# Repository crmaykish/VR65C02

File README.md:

# VR65C02
A 6502 computer system with an ATmega4809 simulating all of the memory and I/O. Two ICs are enough to run native 6502 code on the real silicon. All of the 6502's interactions with the outside world go through the microcontroller.

It's like the 6502 is wearing the ATmega as a VR headset! (AVR headset?)

## Background

### TL;DR

- Real 6502 code running on a real 6502
- ATmega4809 microcontroller emulates everything else
- 6502 is programmed by uploading an Arduino sketch
- 5KB of emulated RAM, up to 32KB emulated ROM
- Memory-mapped UART, GPIO, and I2C peripherals for the 6502
- Eye-watering clock speed of ~250 kHz!

### Why?

Why not? This project started as a weekend experiment to see if I could run a 6502 CPU without having to use a real ROM chip. That quickly turned into "Can I run 6502 code on a real CPU without any real memory or peripherals attached. The answer is yes.

This computer is not fast. It's not practical, but it is kind of fun.

### Why not a Raspberry Pi Pico or FPGA?

Those would both likely be better choices, but to be totally honest, the availability of the ATmega4809 in a 40 pin DIP package is what sold me. I like the aesthetic of two DIP ICs. That's really it.

## Features

### Memory Emulation

VR65C02 is a fully functional computer system. The ATmega microcontroller provides emulated RAM and ROM as well as a passthrough UART and four GPIO pins that the 6502 can access.

The microcontroller controls the RESET and CLOCK lines of the CPU, so all memory access is handled synchronously by the Arduino code. For each bus cycle, the microcontroller reads the address bus and R/W pin from the CPU. If the CPU is reading a memory address, the microcontroller will decode the address into a memory value or an I/O operation and write the appropriate value out to the data bus. On a write cycle, the microcontroller reads the data bus value into its simulated RAM or updates the appropriate I/O system. The microcontroller implements address decoding in code in a similar way to a traditional system using logic gates or PLDs.

Both RAM and ROM are backed by large byte arrays in the microcontroller's memory, the RAM using onboard SRAM and the ROM using onboard Flash.

### I/O Emulation

The UART is a memory-mapped I/O device from the perspective of the 6502, similar to a 6551 ACIA. The CPU can read and write bytes and the microcontroller passes them through to one of its native serial ports.

Similarly, there are four GPIO pins accessible as a memory-mapped register to the 6502.

These GPIO ports have two alternate functions. If SOFT_RESET is defined in [memory_map.h](src/6502_vr_goggles/memory_map.h), then GPIO pin 0 will function as a reset pin for the 6502. It does not reset the Arduino, but it triggers the Arduino to reset the 6502. If soft reset is enabled, pin 0 cannot be used as a normal GPIO pin.

I2C devices can also be attached to the GPIO pins. GPIO 2 and 3 double as SDA and SCL respectively. The Arduino provides low level access to the I2C bus through a few memory-mapped registers. The 6502 can enable/disable the I2C bus, set the active peripheral address, and read/write data through these registers.

See [memory_map.h](src/6502_vr_goggles/memory_map.h) for more details.

It should also be possible to implement SPI passthrough in a similar fashion, but I2C is really a better fit for this system, especially considering its slow clock speed and lack of I/O lines. With I2C, a ton of peripherals can be daisy-chained and there is still room for 1 or 2 GPIO pins. I've tested reading a real-time clock module over I2C from the 6502 code (see the `time` command in [monitor.c](src/monitor.c)).

### Memory Map

The memory map of the 6502 is as follows:
1. 5KB "RAM" at 0x0000
2. I/O regisers at 0x7F00
3. 8KB "ROM" at 0xE000

The ATmega4809 has enough flash memory to support up to 32KB of ROM if necessary, but the total onboard SRAM is only 6KB and some is set aside for the Arduino code.

## Software

The core of VR65C02 is the Arduino sketch running on the ATmega4809. As described above, this program simulates the entire bus cycle of the physical 6502 CPU and all of the memory and I/O interactions.

Real 6502 machine code is running on the CPU. This can be assembly or C code compiled with cc65. Since there is no physical ROM or RAM, the code has to live somewhere. My approach is to use the large amount of onboard Flash memory of the ATmega to store this. The main trick of VR65C02 is taking this compiled binary and getting it into the microcontroller Flash as part of the Arduino sketch upload.

### Setup

To build and deploy code to the VR65C02, you'll need to setup the following:
1. Install Arduino to `/opt/local`
2. Install MegaCoreX Arduino package
3. Install cc65 or some other 6502 compiler/assembler
4. Install make (`build-essential` on Debian/Ubuntu)
5. Install Python 3.x

Note: you may need to update the build.sh script if you're on a different platform. Windows will probably require a different approach.

### Building

The build process is done in a single script, [build.sh](src/build.sh). The process looks like this:
1. Compile 6502 C code into a binary ROM file.
2. Run a Python script to convert this binary file into a C header file with a large const array of bytes.
3. Compile the Arduino sketch with this generated header file.
4. Upload Arduino sketch to microcontroller with new 6502 code.

### Programming the ATmega (and by extension the 6502)

Programming the ATmega4809 is done via UPDI. UPDI is a one-wire programming interface that can be implemented over a simple serial port. On VR65C02, the wiring is already done on the board, so a standard FTDI-style USB-UART can be plugged into the onboard UPDI header. In the Arduino IDE, the SerialUPDI programmer included in MegaCoreX at 230400 baud will work just fine. Make sure to set the serial port to the UPDI USB device and not the one plugged into the UART port.

Note: the board and programmer selection is already done in the [build.sh](src/build.sh) script using the `arduino-cli` command.

It's possible to use a single FTDI device and switch between the headers on board for programming versus serial monitoring, but having two different serial ports is a lot more convenient.

## Limitations

All of the limitations of this system come down to hitting the limits of the ATmega4809 itself in one way or another.

### Clock Speed

The main drawback is obviously clock speed. Simulating the whole bus cycle and all of the potential memory and I/O operations of the 6502 on a 20 MHz 8-bit microcontroller is not exactly quick. Measuring the PHI2 output on the CPU with an oscilloscope shows that the effective clock speed is about 257 kHz. Even at this speed, VR65C02 is surprisingly usable for simple GPIO tasks or interacting over the serial port, but it's about 4x slower than a Commodore 64 or Apple II.

Because not all the emulated peripherals respond at the same speed, the effective clock speed is actually somewhat variable depending on the I/O demands of the 6502 code. This doesn't fluctuate too dramatically, but heavy I/O, e.g. polling the serial port, will run at around 257 kHz, whereas no I/O at all will get the clock up to about 270 kHz.

### Not Enough Pins

Besides the slow speed, the other main limitations is the lack of available pins on the ATmega. All 31 available IO pins are being used to connect to the 6502 bus and control signals. Two of the pins are used for the serial port and four are set up as GPIO. The GPIO pins could be used for other things, but there's not a huge number to spare.

In theory, these GPIO pins could be repurposed as chip-select signals to attach some real I/O devices to the system. It wouldn't be a stretch to attach a real RAM chip and have the microcontroller copy the program code from Flash into that RAM. In that scenario, a real clock oscillator could be used and the Arduino would become a slow peripheral using the RDY pin to handle the higher clock rate.

The ATmega4809 is also available in a 48 pin QFP package with quite a few more I/O pins. This might be fun to explore, but it would definitely detract from the DIP aesthetic and make VR65C02 harder to build.

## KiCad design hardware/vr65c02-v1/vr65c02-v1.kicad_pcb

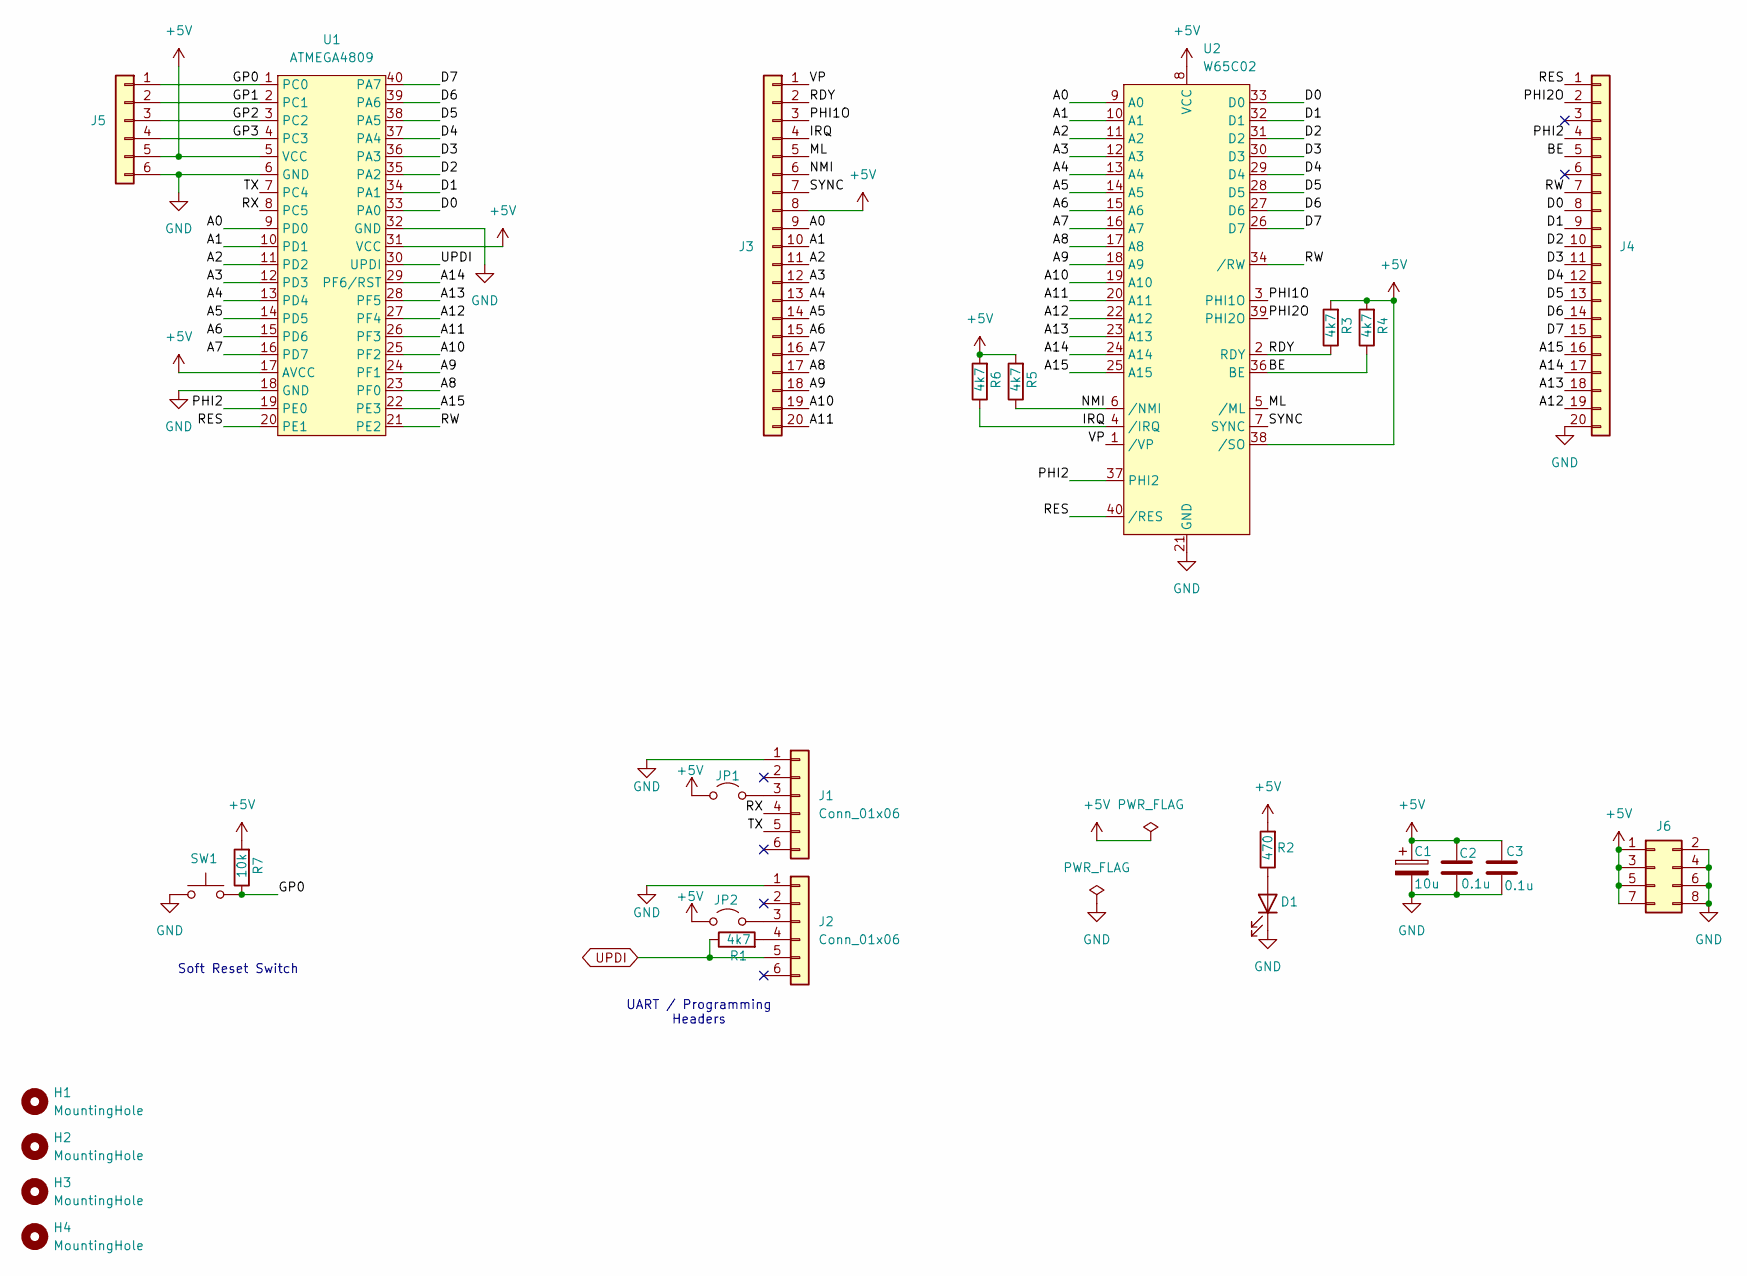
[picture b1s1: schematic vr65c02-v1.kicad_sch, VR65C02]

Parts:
C1: 10u; CP_Radial_D5.0mm_P2.50mm
C2, C3: 0.1u; C_Disc_D4.7mm_W2.5mm_P5.00mm
D1: LED; LED_D5.0mm
H1, H2, H3, H4: MountingHole; MountingHole_3.2mm_M3
J1, J2: Conn_01x06; PinSocket_1x06_P2.54mm_Vertical
J3, J4: Conn_01x20; PinHeader_1x20_P2.54mm_Vertical
J5: Conn_01x06; PinHeader_1x06_P2.54mm_Vertical
J6: Conn_02x04_Odd_Even; PinHeader_2x04_P2.54mm_Vertical
JP1, JP2: Jumper_2_Open; PinHeader_1x02_P2.54mm_Vertical
R1, R3, R4, R5, R6: 4k7; R_Axial_DIN0207_L6.3mm_D2.5mm_P7.62mm_Horizontal
R2: 470; R_Axial_DIN0207_L6.3mm_D2.5mm_P7.62mm_Horizontal
R7: 10k; R_Axial_DIN0207_L6.3mm_D2.5mm_P7.62mm_Horizontal
SW1: SW_Push; SW_PUSH_6mm_H5mm
U1: ATMEGA4809; DIP-40_W15.24mm
U2: W65C02; DIP-40_W15.24mm

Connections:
+5V: C1.1, C2.1, C3.1, J3.8, J5.5, J6.1, J6.3, J6.5, J6.7, JP1.1 (A), JP2.1 (A), R2.2, R3.2, R4.2, R5.2, R6.2, R7.2, U1.5 (VCC), U1.17 (AVCC), U1.31 (VCC), U2.8 (VCC), U2.38 (/SO)
/A0: J3.9, U1.9 (PD0), U2.9 (A0)
/A1: J3.10, U1.10 (PD1), U2.10 (A1)
/A2: J3.11, U1.11 (PD2), U2.11 (A2)
/A3: J3.12, U1.12 (PD3), U2.12 (A3)
/A4: J3.13, U1.13 (PD4), U2.13 (A4)
/A5: J3.14, U1.14 (PD5), U2.14 (A5)
/A6: J3.15, U1.15 (PD6), U2.15 (A6)
/A7: J3.16, U1.16 (PD7), U2.16 (A7)
/A8: J3.17, U1.23 (PF0), U2.17 (A8)
/A9: J3.18, U1.24 (PF1), U2.18 (A9)
/A10: J3.19, U1.25 (PF2), U2.19 (A10)
/A11: J3.20, U1.26 (PF3), U2.20 (A11)
/A12: J4.19, U1.27 (PF4), U2.22 (A12)
/A13: J4.18, U1.28 (PF5), U2.23 (A13)
/A14: J4.17, U1.29 (PF6/RST), U2.24 (A14)
/A15: J4.16, U1.22 (PE3), U2.25 (A15)
/BE: J4.5, R4.1, U2.36 (BE)
/D0: J4.8, U1.33 (PA0), U2.33 (D0)
/D1: J4.9, U1.34 (PA1), U2.32 (D1)
/D2: J4.10, U1.35 (PA2), U2.31 (D2)
/D3: J4.11, U1.36 (PA3), U2.30 (D3)
/D4: J4.12, U1.37 (PA4), U2.29 (D4)
/D5: J4.13, U1.38 (PA5), U2.28 (D5)
/D6: J4.14, U1.39 (PA6), U2.27 (D6)
/D7: J4.15, U1.40 (PA7), U2.26 (D7)
/GP0: J5.1, R7.1, SW1.2, U1.1 (PC0)
/GP1: J5.2, U1.2 (PC1)
/GP2: J5.3, U1.3 (PC2)
/GP3: J5.4, U1.4 (PC3)
/IRQ: J3.4, R6.1, U2.4 (/IRQ)
/ML: J3.5, U2.5 (/ML)
/NMI: J3.6, R5.1, U2.6 (/NMI)
/PHI1O: J3.3, U2.3 (PHI1O)
/PHI2: J4.4, U1.19 (PE0), U2.37 (PHI2)
/PHI2O: J4.2, U2.39 (PHI2O)
/RDY: J3.2, R3.1, U2.2 (RDY)
/RES: J4.1, U1.20 (PE1), U2.40 (/RES)
/RW: J4.7, U1.21 (PE2), U2.34 (/RW)
/RX: J1.4, U1.8 (PC5)
/SYNC: J3.7, U2.7 (SYNC)
/TX: J1.5, U1.7 (PC4)
/VP: J3.1, U2.1 (/VP)
GND: C1.2, C2.2, C3.2, D1.1 (K), J1.1, J2.1, J4.20, J5.6, J6.2, J6.4, J6.6, J6.8, SW1.1, U1.6 (GND), U1.18 (GND), U1.32 (GND), U2.21 (GND)
unnamed: D1.2 (A), R2.1
unnamed: J1.3, JP1.2 (B)
unnamed: J2.3, JP2.2 (B)
unnamed: J2.4, R1.2
UPDI: J2.5, R1.1, U1.30 (UPDI)

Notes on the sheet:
Soft Reset Switch
UART / Programming Headers

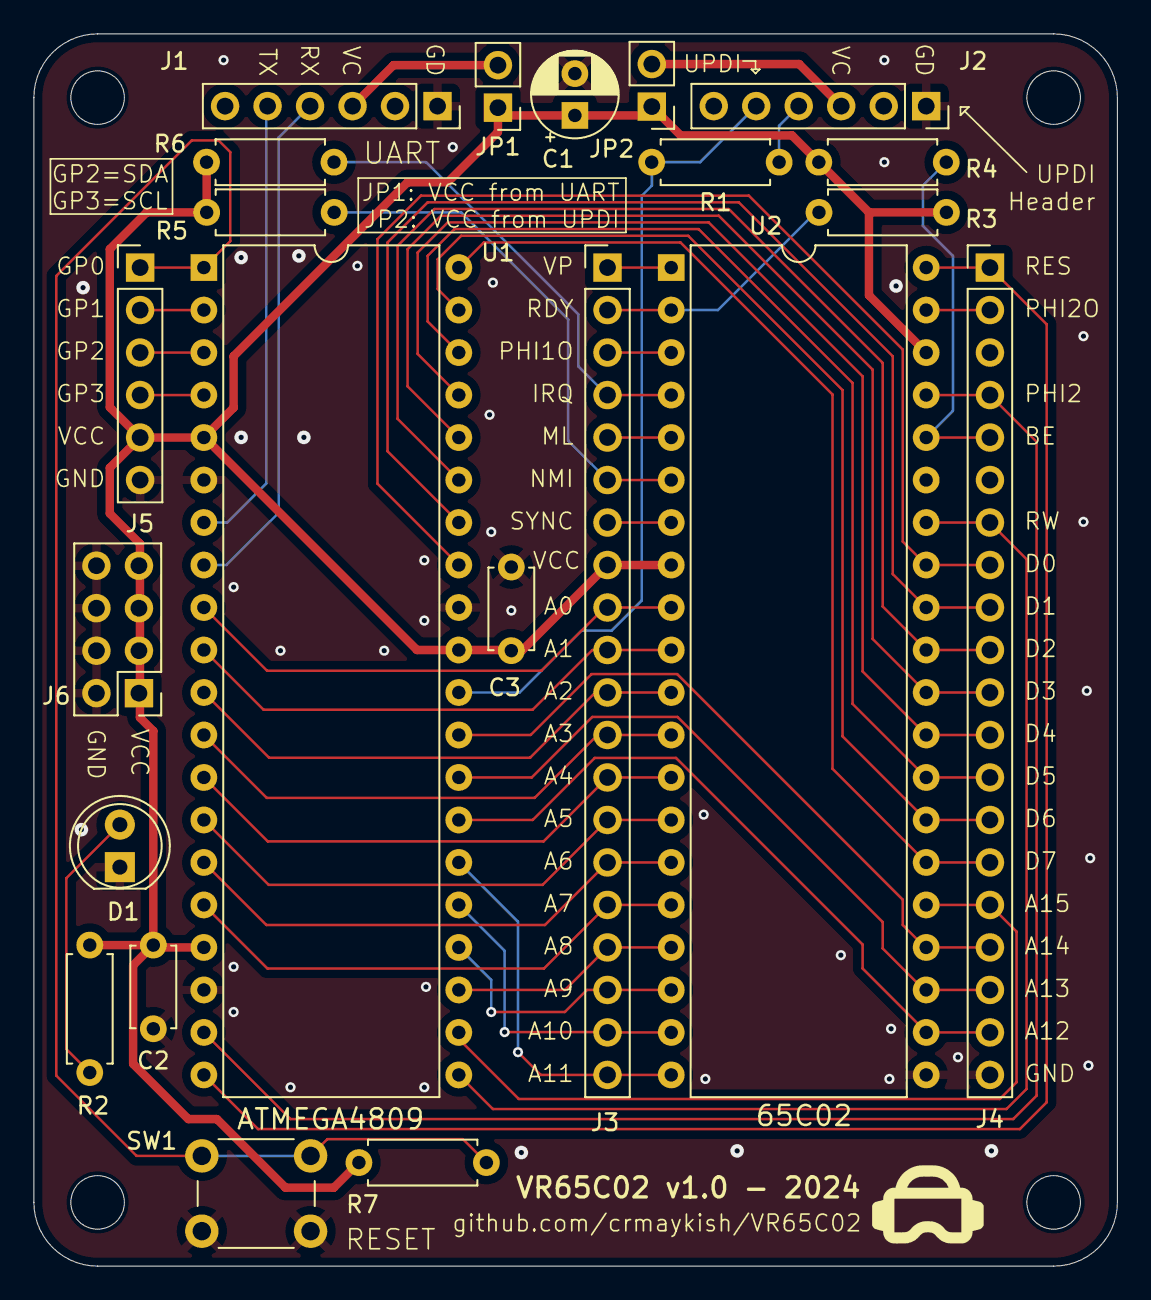
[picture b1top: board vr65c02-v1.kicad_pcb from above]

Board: 2 copper layers, 64.8 x 73.7 mm, 26 parts (0 on the bottom side), 49 nets.

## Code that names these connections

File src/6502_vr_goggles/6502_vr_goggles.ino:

#include "6502_rom_bin.h"
#include "memory_map.h"
#include <Wire.h>

// MCU pins
#ifdef SOFT_RESET
#define SOFT_RES_SW PIN_PC0
#endif

// CPU control pins
#define RESB PIN_PE1
#define CLK PIN_PE0
#define RWB PIN_PE2

// CPU buses
#define DATA_BUS VPORTA
#define ADDR_LOW VPORTD
#define ADDR_HIGH VPORTF
#define A15 PIN_PE3
#define VIA_PORT PORTC

// Byte array acts as system RAM for the 6502
uint8_t RAM[RAM_SIZE] = {0};

// NOTE: ROM content is defined in the generated header file 6502_rom_bin.h

uint16_t addr = 0;
uint8_t data = 0;
bool rw = 0;

uint8_t i2c_dev = 0;

void reset_6502() {
    digitalWriteFast(RESB, LOW);

    // Toggle the clock a few times with the reset pin LOW
    for (int i = 0; i < 50; i++) {
        digitalWriteFast(CLK, LOW);
        delay(2);
        digitalWriteFast(CLK, HIGH);
        delay(2);
    }

    // Take 6502 out of reset
    digitalWriteFast(RESB, HIGH);
}

void setup() {
    // Setup buses as input
    ADDR_LOW.DIR = 0;
    ADDR_HIGH.DIR = 0;
    DATA_BUS.DIR = 0;
    pinMode(A15, INPUT);

    // Setup CPU control pins
    pinMode(RWB, INPUT);
    pinMode(RESB, OUTPUT);
    pinMode(CLK, OUTPUT);
    digitalWriteFast(RESB, LOW);
    digitalWriteFast(CLK, HIGH);

    // Setup "VIA" pins
    VIA_PORT.DIRCLR = 0b00001111;

#ifdef SOFT_RESET
    pinMode(SOFT_RES_SW, INPUT);
#endif

    Serial1.swap(1);
    Serial1.begin(115200);

    reset_6502();
}

void loop() {
#ifdef SOFT_RESET
    if (!digitalReadFast(SOFT_RES_SW)) {
        reset_6502();
    }
#endif

    // PHI goes LOW
    digitalWriteFast(CLK, LOW);

    // Delay slightly, giving the 6502 time to react to the falling clock edge
    // before reading the buses
    asm("nop");
    asm("nop");

    rw = digitalReadFast(RWB);
    addr = (digitalReadFast(A15) << 15) | (ADDR_HIGH.IN << 8) | ADDR_LOW.IN;

    if (rw) {
        // 6502 is reading from memory
        DATA_BUS.DIR = 0xFF;

        if (addr >= ROM_START) {
            // Read from "ROM"
            DATA_BUS.OUT = ROM[addr % ROM_SIZE];
        } else if (addr < RAM_SIZE) {
            // Read from "RAM"
            DATA_BUS.OUT = RAM[addr];
        } else if (addr == UART_RX_RDY) {
            // Read from UART RX ready register
            DATA_BUS.OUT = (Serial1.available() > 0) ? 0x01 : 0x00;
        } else if (addr == UART_RX) {
            // Read from serial port
            DATA_BUS.OUT = Serial1.read();
        } else if (addr == VIA) {
            // Read from VIA GPIO
            DATA_BUS.OUT = VIA_PORT.IN & 0xF;
        } else if (addr == VIA_DIR) {
            // Read from VIA direction register
            DATA_BUS.OUT = VIA_PORT.DIR & 0xF;
        } else if (addr == I2C_DATA) {
            Wire.requestFrom(i2c_dev, 1);
            if (Wire.available()) {
                DATA_BUS.OUT = Wire.read();
            } else {
                DATA_BUS.OUT = 0;
            }
        } else if (addr == I2C_ADDR) {
            DATA_BUS.OUT = i2c_dev;
        }
    } else {
        // 6502 is writing to memory
        DATA_BUS.DIR = 0x00;
    }

    // PHI goes HIGH
    digitalWriteFast(CLK, HIGH);
    // NOTE: The 6502 does not seem to require a delay on the rising edge
    // of the clock like it does on the falling edge

    if (!rw) {
        // Read the data bus
        data = DATA_BUS.IN;

        if (addr < RAM_SIZE) {
            // Write data bus to "RAM"
            RAM[addr] = data;
        } else if (addr == UART_TX) {
            // Write data bus to UART
            Serial1.write(data);
        } else if (addr == VIA) {
            // Write data bus to "VIA"
            VIA_PORT.OUT = (data & 0xF);
        } else if (addr == VIA_DIR) {
            // Write to VIA GPIO direction register
#ifdef SOFT_RESET
            // If soft reset switch is active, ignore the lowest bit
            VIA_PORT.DIRCLR = 0b00001110;
            VIA_PORT.DIRSET = data & 0b00001110;
#else
            // Otherwise, use the lowest four bits of the port as GPIO
            VIA_PORT.DIRCLR = 0xF;
            VIA_PORT.DIRSET = data & 0xF;
#endif
        } else if (addr == I2C_CTRL) {
            // Turn on or off the I2C function of the GPIO pins
            if (data & 0b01) {
                Wire.swap(1);
                Wire.begin();
            } else {
                Wire.end();
            }
        } else if (addr == I2C_ADDR) {
            // Set I2C device address
            i2c_dev = data;
        } else if (addr == I2C_DATA) {
            // Write a byte to active I2C device
            Wire.beginTransmission(i2c_dev);
            Wire.write(data);
            Wire.endTransmission();
        }
    }
}

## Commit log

2024-08-25 Emulating ROM, RAM, serial, and GPIO
2024-08-25 Copying 6502 binary to AVR flash memory as part of Arduino upload
2024-08-25 65C02 is running C code with stdlib support
2024-08-26 Document the prototype
2024-08-26 Move code into src folder
2024-08-26 Stubbed out schematic
2024-08-26 Increased effective clock speed to 183kHz
2024-08-26 Add uart_getc function
2024-08-27 Add clang-format
2024-08-27 Photo of soldered prototype
2024-08-27 Minor pinout change
2024-08-27 Code optimization, running at 257kHz
2024-08-27 Clarification on clock speed
2024-08-27 Switch to alternate UART pins
2024-08-27 Memory mapped now shared between Arduino and 6502 code
2024-08-27 Fix make clean
2024-08-28 Ported simple ROM monitor
2024-08-28 VIA pins are now bidrectional
2024-08-28 Add a simple demo command to the monitor
2024-09-05 PCB v1 routed
2024-09-05 Add PCB render to README
2024-09-06 Basic soft reset button option
2024-09-07 Implement I2C passthrough to 6502
2024-09-07 PCB release v1.0a
2024-09-07 Render of PCB v1.0
2024-09-20 Add PCB images
